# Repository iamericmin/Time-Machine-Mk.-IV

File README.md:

# Time Machine Mk. IV
# [Full write-up is on my website!](https://iamericmin.github.io/tm4.html)

## Homebrew cyberpunk Cortex M4 "smart"watch with BLE radio

Project status: all bugs not fixed before January 1st 2020 are now officially features

# Hi!
I am Eric Min and I'm a 18 year old teenager from Seoul, South Korea. This is my first major project in circuit design and firmware development. It is a cyberpunk inspired wristwatch leveraging the low-power and Bluetooth Low Energy features of Nordic's nRF52832. I think it looks pretty dope! :)

# THE JUICY STUFF:
-   PROCESSOR: nRF52832 Soc. 64MHz ARM cortex M4 with 64k RAM and 512k flash.
-   FIRMWARE: Espruino JS interpreter + JS code layer
-   POWER: 12mm CR1225 coin cell battery. About two weeks of battery life.
-   DISPLAY: If you can call it a display. Dual 7-segment LEDs with five auxiliary LEDs.
-   INPUT: Triple momentary tactile switches.
-   SOUND: Mini piezo speaker.
-   DIMENSIONS: 43.18mm width and length, 10.2mm thickness.
-   STRAP: 22mm NATO strap.

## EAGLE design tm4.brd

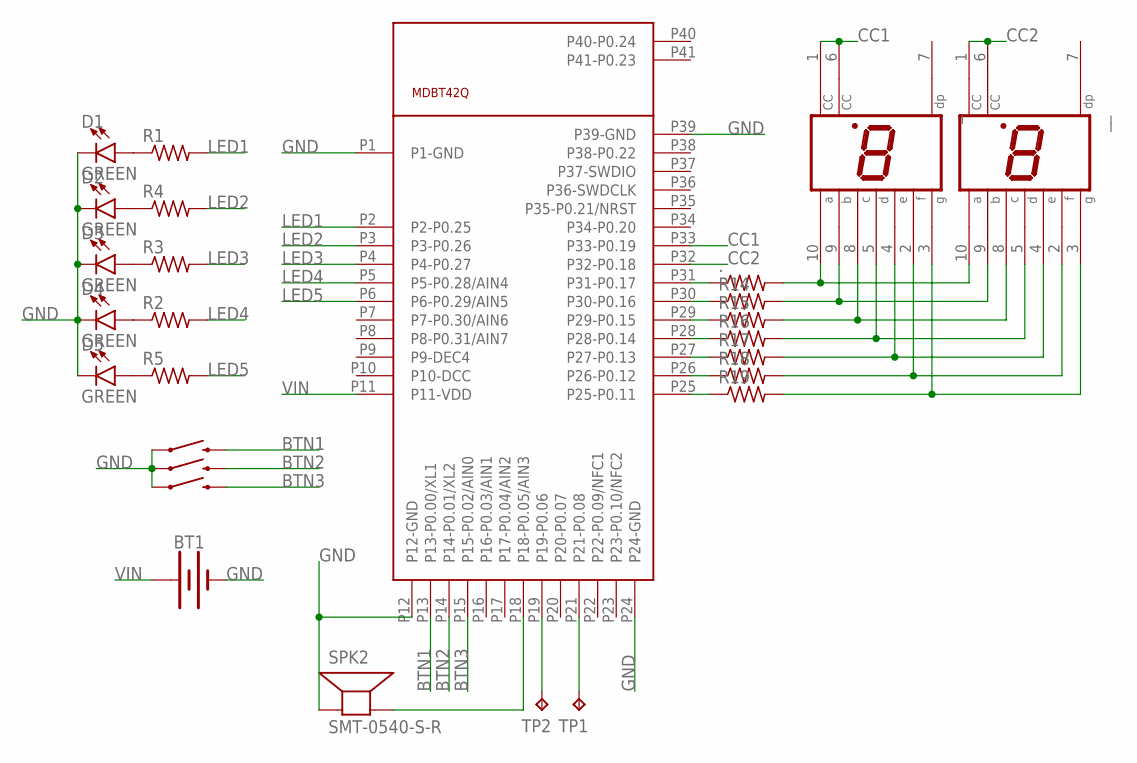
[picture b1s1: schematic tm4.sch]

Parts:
.: R-US_M0805; M0805
BT1: BATTERY-12MM_SMD; BATTCON_12MM
D1, D2, D3, D4, D5: GREEN; LED-1206
R1, R2, R3, R4, R5, R14, R15, R16, R17, R18, R19: R-US_M0805; M0805
SPK2: SMT-0540-S-R
TP1, TP2: TPTP19R; TP19R
U$1: MDBT42Q; MDBT40
_: HD-A103; HDSP-A
__: HD-A103; HDSP-A
____: MOMENTARY-SWITCH-SPST-SMD-6.2MM-TALL; TACTILE_SWITCH_SMD_6.2MM_TALL
_____: MOMENTARY-SWITCH-SPST-SMD-6.2MM-TALL; TACTILE_SWITCH_SMD_6.2MM_TALL
______: MOMENTARY-SWITCH-SPST-SMD-6.2MM-TALL; TACTILE_SWITCH_SMD_6.2MM_TALL

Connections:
A: ..2, _.10 (A), __.10 (A)
B: R14.2, _.9 (B), __.9 (B)
BTN1: U$1.P13 (P13-P0.00/XL1), ____.B2 (2)
BTN2: U$1.P14 (P14-P0.01/XL2), _____.B2 (2)
BTN3: U$1.P15 (P15-P0.02/AIN0), ______.B2 (2)
C: R15.2, _.8 (C), __.8 (C)
CC1: U$1.P33 (P33-P0.19), _.1 (CC), _.6 (CC)
CC2: U$1.P32 (P32-P0.18), __.1 (CC), __.6 (CC)
D: R16.2, _.5 (D), __.5 (D)
E: R17.2, _.4 (E), __.4 (E)
F: R18.2, _.2 (F), __.2 (F)
G: R19.2, _.3 (G), __.3 (G)
GND: BT1.GND (-), D1.C, D2.C, D3.C, D4.C, D5.C, SPK2.- (+), U$1.P1 (P1-GND), U$1.P12 (P12-GND), U$1.P24 (P24-GND), U$1.P39 (P39-GND), ____.A2 (1), _____.A2 (1), ______.A2 (1)
LED1: R1.2, U$1.P2 (P2-P0.25)
LED2: R4.2, U$1.P3 (P3-P0.26)
LED3: R3.2, U$1.P4 (P4-P0.27)
LED4: R2.2, U$1.P5 (P5-P0.28/AIN4)
LED5: R5.2, U$1.P6 (P6-P0.29/AIN5)
unnamed: ..1, U$1.P31 (P31-P0.17)
unnamed: R14.1, U$1.P30 (P30-P0.16)
unnamed: R15.1, U$1.P29 (P29-P0.15)
unnamed: D1.A, R1.1
unnamed: D2.A, R4.1
unnamed: D3.A, R3.1
unnamed: D4.A, R2.1
unnamed: R16.1, U$1.P28 (P28-P0.14)
unnamed: R17.1, U$1.P27 (P27-P0.13)
unnamed: R18.1, U$1.P26 (P26-P0.12)
unnamed: R19.1, U$1.P25 (P25-P0.11)
unnamed: SPK2.+ (-), U$1.P18 (P18-P0.05/AIN3)
unnamed: D5.A, R5.1
unnamed: TP1.TP, U$1.P21 (P21-P0.08)
unnamed: TP2.TP, U$1.P19 (P19-P0.06)
VIN: BT1.PWR@1 (+), U$1.P11 (P11-VDD)

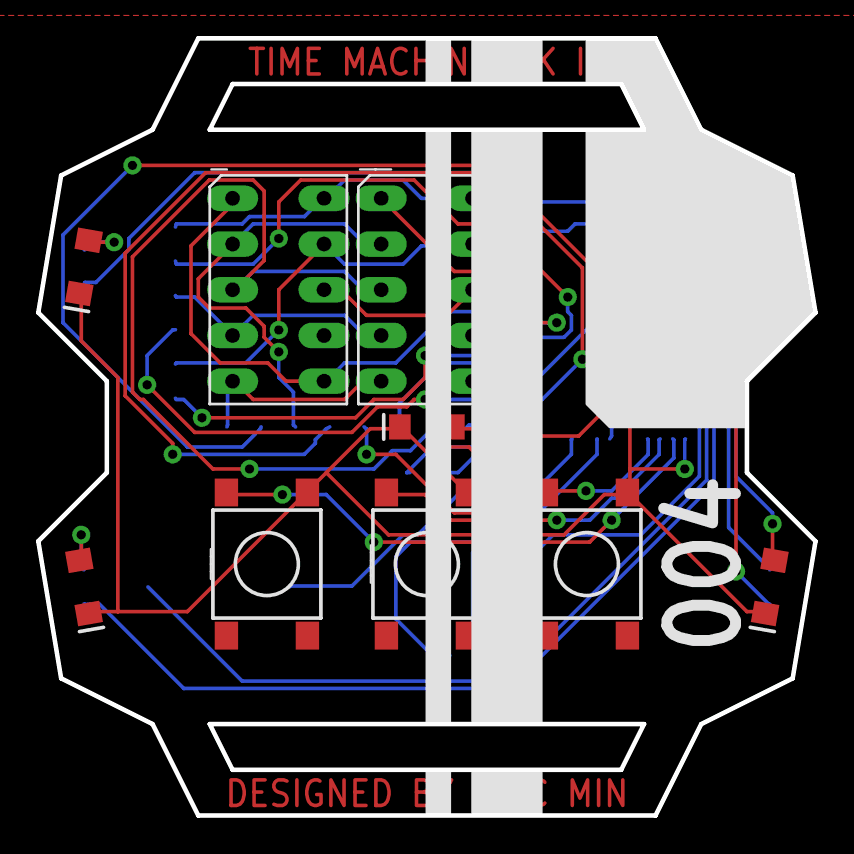
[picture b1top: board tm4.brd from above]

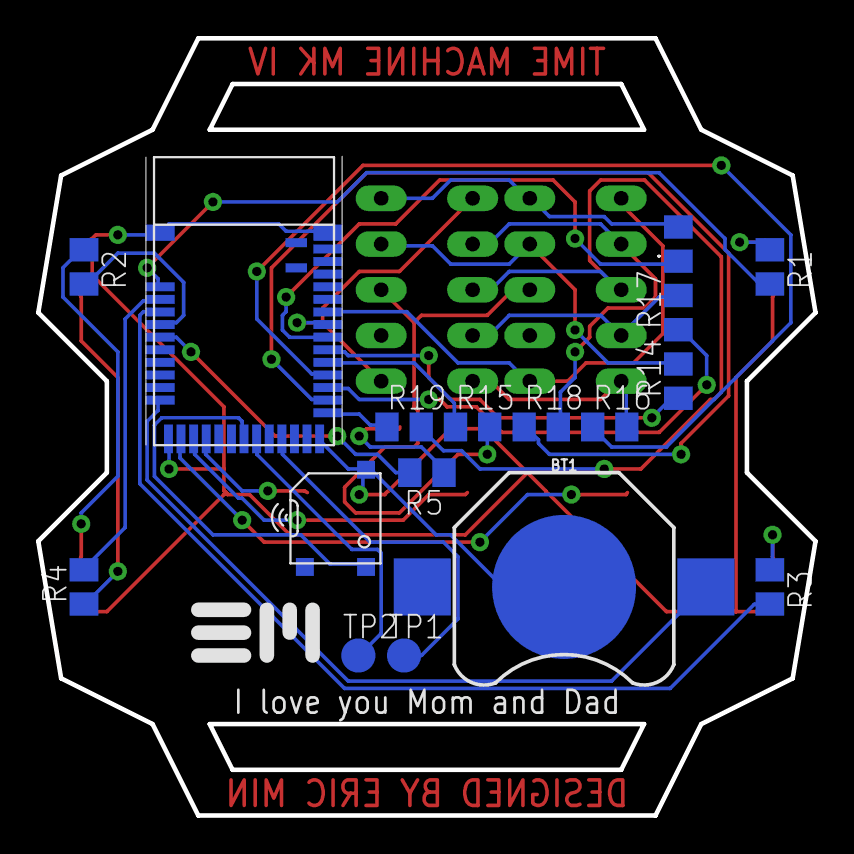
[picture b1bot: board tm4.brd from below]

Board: 2 copper layers, 43.2 x 43.2 mm, 27 parts (17 on the bottom side), 34 nets.

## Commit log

2019-06-06 tm4 source
2019-06-17 updated tm4.js
2019-07-07 updated js firmware
2019-07-07 updated js script, super buggy

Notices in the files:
parts and their libraries:
SparkFun-Batteries: Licensing: Creative Commons ShareAlike 4.0 International - https://creativecommons.org/licenses/by-sa/4.0
